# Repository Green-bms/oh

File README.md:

# OH!

OH! is a video magazine of Opensource Hardware projects streaming for free on @oh_video Youtube channel.

## 2024 edition
### Issue 01 - Play with NeoMatrix
Streaming release date: 02/01/2024 <br>

Youtube page: https://youtu.be/Kcz4IKiXUUs?si=wSDmESj03bVOOBnR <br>

In this issue we see how to program the WS2812B 8x8 RGB LED matrices.<br>

Resources: https://github.com/Green-bms/oh/tree/master/2024%20edition/Issue%201

### Issue 02 - Stop If Crash Watchdog
Streaming release date: 13/01/2024 <br>

Youtube page: https://youtu.be/fLkRN2xnHXY?si=DeNB-EbN8AmZp_JL <br>

In this issue I present my project "Stop If Crash", a simple Watchdog circuit based on IC NE555.
We will see together a simulation of the circuit, the design of the PCB with Kicad, the assembly with the functional test in the laboratory.<br>

Resources: https://github.com/Green-bms/oh/tree/master/2024%20edition/Issue%2002

### Issue 03 - OpticalShow
Streaming release date: 30/01/2024 <br>

Youtube page: https://youtu.be/mVdG0zdTeCE?si=hjvFPSwVRxgswea1 <br>

OpticalShow is a system that uses optical fibers to transmit the light emitted by an RGB LED matrix.
Each fiber is associated with its own LED and allows you to remote its RGB light to animate projects, such as panels, maps, artistic objects and wearables.
in this issue, in addition to describing the OpticalShow system, I show two application examples: "The world is mine!", a map of the world animated and illuminated by optical fibers and "Gloween Show" a small panel used in the Halloween party.<br>

Resources: 

- OpticalShow.
Hackaday: https://hackaday.io/project/189963-opticalshow<br>
Github: https://github.com/Green-bms/OpticalShow<br>
You can buy mask here: https://www.pcbway.com/project/shareproject/OpticalShow_mask_225f24a0.html<br>
You can buy card here: https://www.pcbway.com/project/shareproject/OpticalShow_card_PCB_6144c0a7.html<br>

- The World is mine.
https://www.instructables.com/The-World-Is-Mine/

- Gloween Show.
https://www.instructables.com/Gloween-Show/

### Issue 04 - CNC PCB milling
Streaming release date: 13/02/2024 <br>

Youtube page: https://www.youtube.com/watch?v=61v8TkvMFBA <br>
Make PCB with CNC milling machine <br>
In this issue I present to you my economical CNC milling machine Vevor CNC 3018 PRO, with which I started making PCBs for my simplest projects.
In addition to describing the milling machine, we will create a small step by step project together, from the CAD drawing of the PCB to the milling!<br>

If you also want to practice with the same PCB shown in the video, you can download all the CAD, CAM and CNC files from the following link:<br>
https://github.com/Green-bms/oh/tree/master/2024%20edition/Issue%2004 <br>

Opensource applications used :<br>
 - Kicad: https://www.kicad.org/ <br>
 - Flatcam: http://flatcam.org/ <br>
 - Candle: https://github.com/Denvi/Candle <br>

### Issue 05 - EV Lithium upgrades
Streaming release date: 27/02/2024 <br>

Youtube page: https://www.youtube.com/watch?v=jmhK0d0eKHg <br>
In this issue I take a trip back in time to tell you about my projects related to electric mobility.
Today there is a lot of talk about electric mobility.
I started to be interested in 2-wheeled electric vehicles in 2013, so I could go to work every day while polluting less!
I gave life back to 3 electric motorbikes that had exhausted batteries, transforming them into high-performance vehicles, with lithium batteries!
The vehicles I upgraded are:
E-tropolis Belair,
Vectrix Vx1 and e-max 110s

I have decided to share with you this exciting experience that lasted 10 years.

I have shared the documents of my upgrades at the following links:
https://github.com/Green-bms/oh/tree/master/2024%20edition/Issue%2005

### Issue 06 - Smart BMS (part 1)
Streaming release date: 12/03/2024 <br>

Youtube page: https://youtu.be/0NjMYVWZLLw?si=yNR26aHXIvKIdVsY <br>
In this issue I start to talk to you about my first Opensource project: Smart BMS - Battery Management System.<br>
I have shared the documents of the project at the following links: <br>
Github: https://github.com/Green-bms/SmartBMS <br>
Hackaday: https://hackaday.io/project/181453-green-bms <br>

### Issue 07 - Smart BMS (part 2)
Streaming release date: 26/03/2024 <br>

Youtube page: https://youtu.be/d0Qe47wP7eQ?si=s2jLH3D_zc0WCvRl  <br>
In this issue I continue to describe my first Opensource project: Smart BMS - Battery Management System <br>
I have shared the documents of the project at the following links: <br>
Github: https://github.com/Green-bms/SmartBMS <br>
Hackaday: https://hackaday.io/project/181453-green-bms <br>

### Issue 08 - Smart BMS (part 3)
Streaming release date: 09/04/2024 <br>

Youtube page: https://youtu.be/FND_0AVq5Ik?si=xOSsRHYRp_0sxjTm <br>
In this issue I continue to describe my first Opensource project: Smart BMS - Battery Management System <br>
I have shared the documents of the project at the following links: <br>
Github: https://github.com/Green-bms/SmartBMS <br>
Hackaday: https://hackaday.io/project/181453-green-bms <br>

### Issue 09 - Green Detect Wireless Sensor Network
Streaming release date: 23/04/2024 <br>

Youtube page: https://youtu.be/QgU09LJju4c?si=UmGGuCsF_K0YVous <br>
In this issue I describe my  Opensource project: Green Detect Wireless Sensor Network Platform (WSN) , for environmental monitoring. <br>
I have shared the documents of the project at the following links: <br>
Github:  https://github.com/Green-bms/GreenDetect <br>
Hackaday: https://hackaday.io/project/186064-green-detect <br>

### Issue 10 - Green Detect Windows application
Streaming release date: 07/05/2024 <br>

Youtube page: https://youtu.be/rTwm69dqrus?si=7FWuEQkdGhM1CUF- <br>
In this issue I describe the Green Detect application in detail.
I show you how to manage and configure the wireless sensor network. <br>
I have shared the documents of the project at the following links: <br>
Github:  https://github.com/Green-bms/GreenDetect <br>
Hackaday: https://hackaday.io/project/186064-green-detect <br>

### Issue 11 - Green Detect Windows application
Streaming release date: 21/05/2024 <br>

Youtube page: https://youtu.be/-PUpspmr6Rk?si=hIGa6V5kiF8c8neI <br>
This issue is dedicated to system tests, we will test a network with 60 modules, fault simulations and a working prototype on the balcony of my house! <br>
I have shared the documents of the project at the following links: <br>
Github:  https://github.com/Green-bms/GreenDetect <br>
Hackaday: https://hackaday.io/project/186064-green-detect <br>

## Warning
All projects, tests and experiments shown and shared in this repository may contain errors and malfunctions and are without warranty.

If you decide to make them, remember that it is at your own risk

The use of this project may not be compliant with local laws or regulations.

## License

This work is licensed under a **Creative Commons Attribution-ShareAlike 4.0 International License**.
https://creativecommons.org/licenses/by-sa/4.0/

### You are free to:

**Share** — copy and redistribute the material in any medium or format

**Adapt**  — remix, transform, and build upon the material
for any purpose, even commercially.
This license is acceptable for Free Cultural Works.
The licensor cannot revoke these freedoms as long as you follow the license terms.

### Under the following terms:

**Attribution** — You must give appropriate credit, provide a link to the license, and indicate if changes were made. You may do so in any reasonable manner, but not in any way that suggests the licensor endorses you or your use.

**ShareAlike** — If you remix, transform, or build upon the material, you must distribute your contributions under the same license as the original.

**No additional restrictions** — You may not apply legal terms or technological measures that legally restrict others from doing anything the license permits.

### Notices:
You do not have to comply with the license for elements of the material in the public domain or where your use is permitted by an applicable exception or limitation.
No warranties are given. The license may not give you all of the permissions necessary for your intended use. For example, other rights such as publicity, privacy, or moral rights may limit how you use the material.

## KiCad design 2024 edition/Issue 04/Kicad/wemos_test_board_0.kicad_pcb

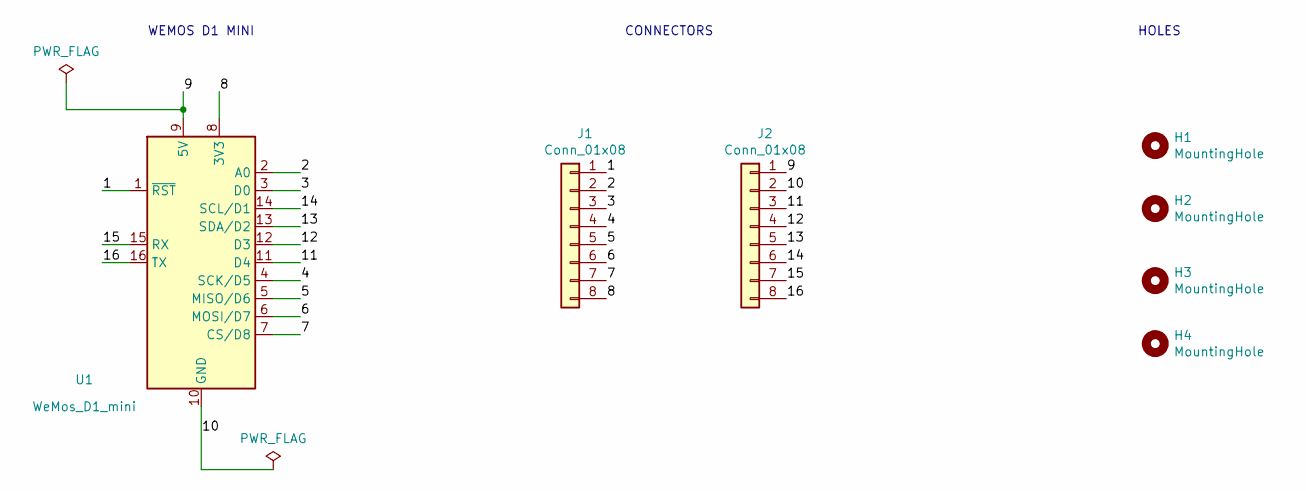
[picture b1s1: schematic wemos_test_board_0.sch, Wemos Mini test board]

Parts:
H1, H2, H3, H4: MountingHole; MountingHole_3.2mm_M3
J1, J2: Conn_01x08; TerminalBlock_Phoenix_PT-1,5-8-5.0-H_1x08_P5.00mm_Horizontal
U1: WeMos_D1_mini; WEMOS_D1_mini_light

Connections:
/1: J1.1, U1.1 (~RST)
/2: J1.2, U1.2 (A0)
/3: J1.3, U1.3 (D0)
/4: J1.4, U1.4 (SCK/D5)
/5: J1.5, U1.5 (MISO/D6)
/6: J1.6, U1.6 (MOSI/D7)
/7: J1.7, U1.7 (CS/D8)
/8: J1.8, U1.8 (3V3)
/9: J2.1, U1.9 (5V)
/10: J2.2, U1.10 (GND)
/11: J2.3, U1.11 (D4)
/12: J2.4, U1.12 (D3)
/13: J2.5, U1.13 (SDA/D2)
/14: J2.6, U1.14 (SCL/D1)
/15: J2.7, U1.15 (RX)
/16: J2.8, U1.16 (TX)

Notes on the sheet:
WEMOS D1 MINI
CONNECTORS
HOLES

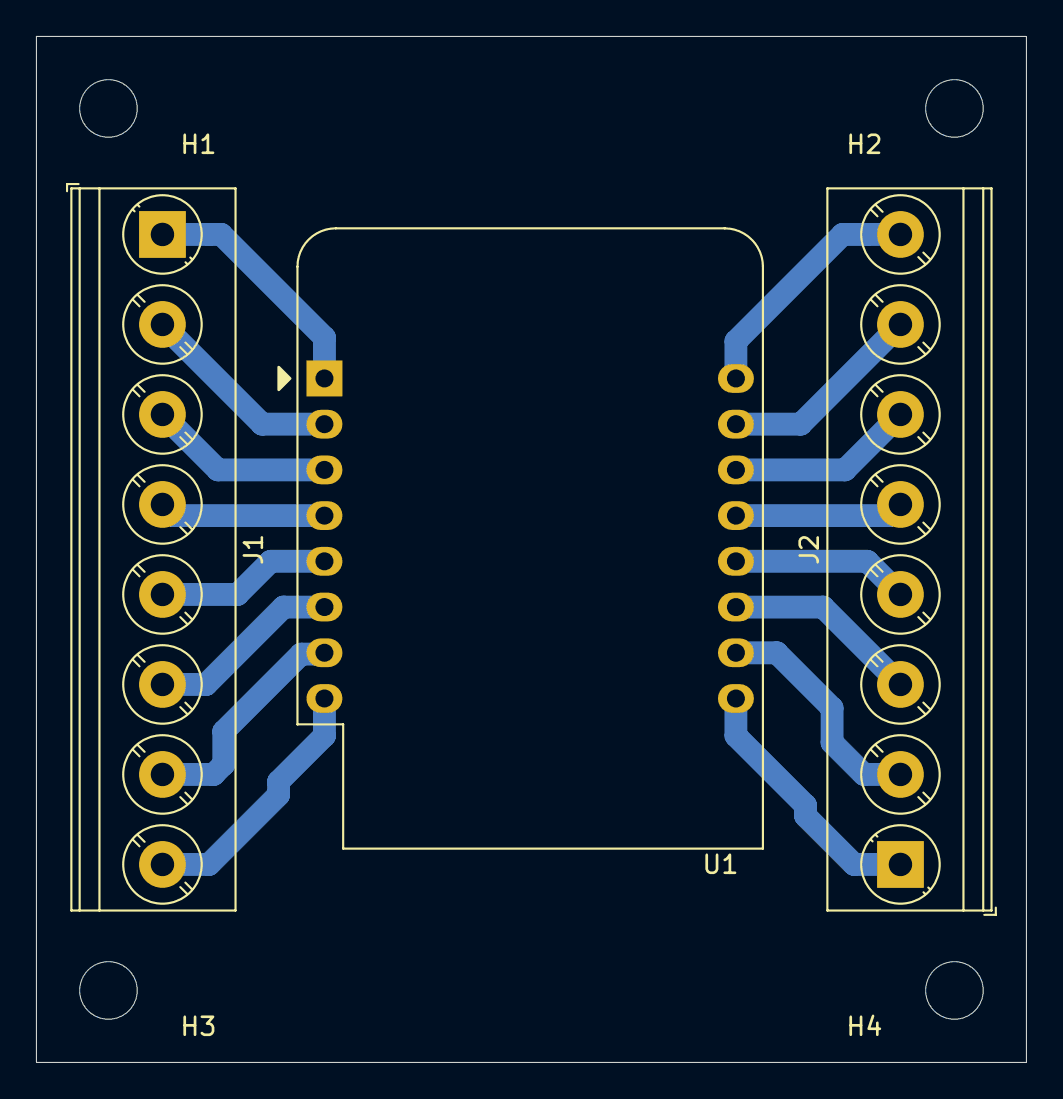
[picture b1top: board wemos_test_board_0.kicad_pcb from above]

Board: 2 copper layers, 55.0 x 57.0 mm, 7 parts (0 on the bottom side), 16 nets.

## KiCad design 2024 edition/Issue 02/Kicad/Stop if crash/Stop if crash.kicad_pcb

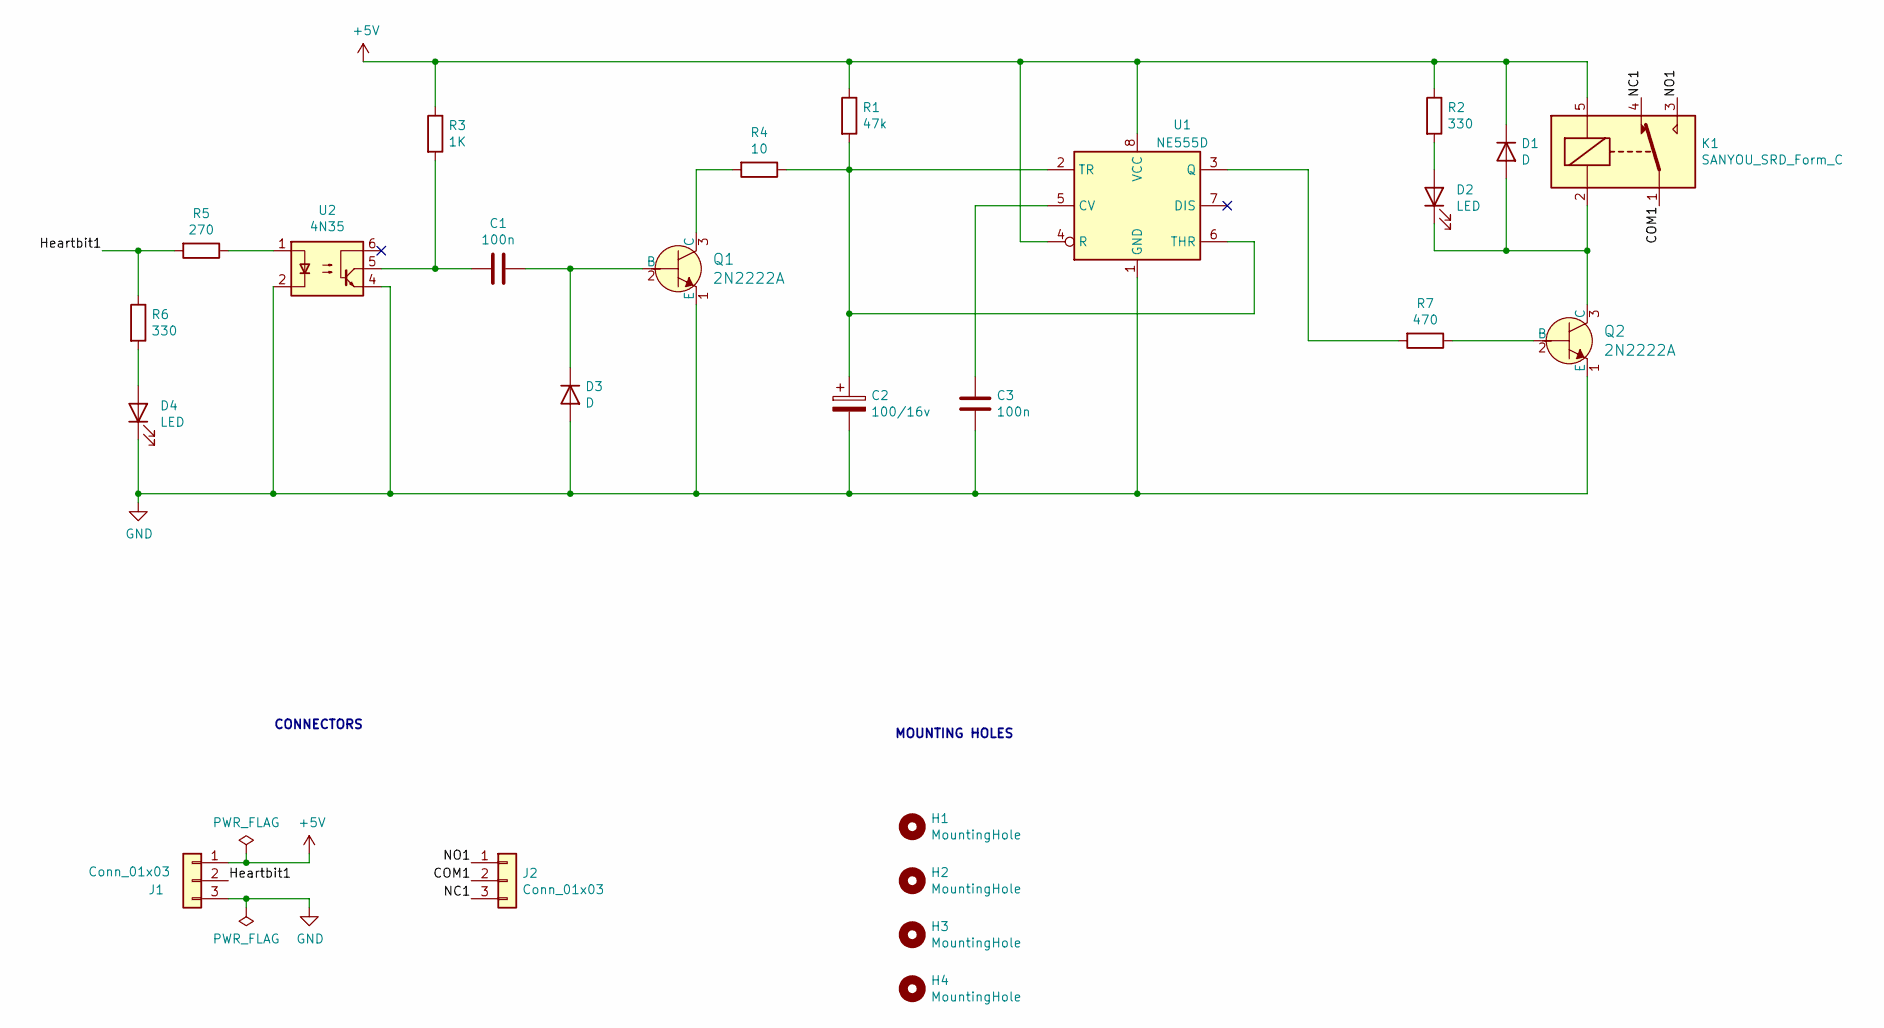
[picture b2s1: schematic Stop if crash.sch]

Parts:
C1, C3: 100n; C_Disc_D4.3mm_W1.9mm_P5.00mm
C2: 100/16v; CP_Radial_D8.0mm_P5.00mm
D1, D3: D; D_DO-15_P2.54mm_Vertical_AnodeUp
D2, D4: LED; LED_D3.0mm
H1, H2, H3, H4: MountingHole; MountingHole_3.2mm_M3
J1, J2: Conn_01x03; TerminalBlock_Phoenix_PT-1,5-3-5.0-H_1x03_P5.00mm_Horizontal
K1: SANYOU_SRD_Form_C; Relay_SPDT_SANYOU_SRD_Series_Form_C
Q1, Q2: 2N2222A; TO-92; MPN 2N2222A; Digi-Key_PN 2N2222ACS-ND
R1: 47k; R_Axial_DIN0207_L6.3mm_D2.5mm_P2.54mm_Vertical
R2, R6: 330; R_Axial_DIN0207_L6.3mm_D2.5mm_P2.54mm_Vertical
R3: 1K; R_Axial_DIN0207_L6.3mm_D2.5mm_P2.54mm_Vertical
R4: 10; R_Axial_DIN0207_L6.3mm_D2.5mm_P2.54mm_Vertical
R5: 270; R_Axial_DIN0207_L6.3mm_D2.5mm_P2.54mm_Vertical
R7: 470; R_Axial_DIN0207_L6.3mm_D2.5mm_P2.54mm_Vertical
U1: NE555D; DIP-8_W7.62mm
U2: 4N35; DIP-6_W7.62mm

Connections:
+5V: D1.1 (K), J1.1, K1.5, R1.1, R2.1, R3.1, U1.4 (R), U1.8 (VCC)
/COM1: J2.2, K1.1
/Heartbit1: J1.2, R5.2, R6.1
/NC1: J2.3, K1.4
/NO1: J2.1, K1.3
GND: C2.2, C3.2, D3.2 (A), D4.1 (K), J1.3, Q1.1 (E), Q2.1 (E), U1.1 (GND), U2.2, U2.4
unnamed: C1.1, D3.1 (K), Q1.2 (B)
unnamed: C1.2, R3.2, U2.5
unnamed: C2.1, R1.2, R4.1, U1.2 (TR), U1.6 (THR)
unnamed: C3.1, U1.5 (CV)
unnamed: D1.2 (A), D2.1 (K), K1.2, Q2.3 (C)
unnamed: D2.2 (A), R2.2
unnamed: D4.2 (A), R6.2
unnamed: Q1.3 (C), R4.2
unnamed: Q2.2 (B), R7.1
unnamed: R5.1, U2.1
unnamed: R7.2, U1.3 (Q)

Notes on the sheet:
CONNECTORS
MOUNTING HOLES

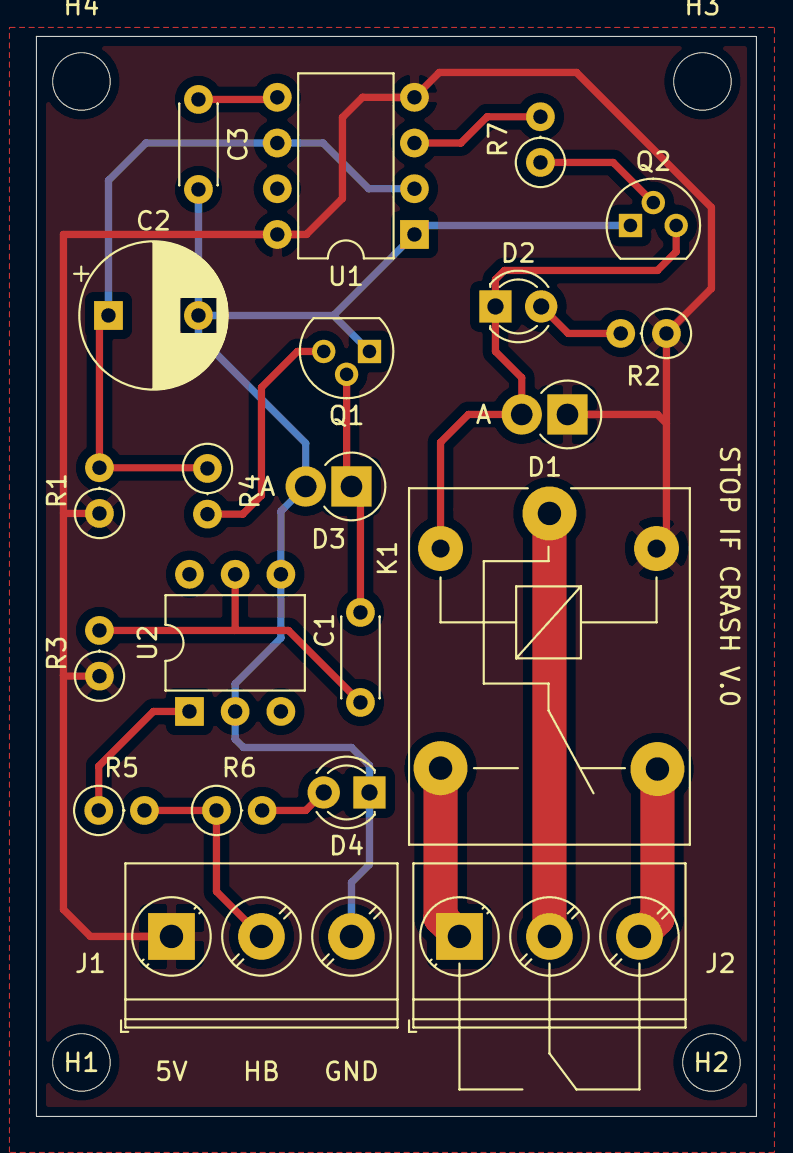
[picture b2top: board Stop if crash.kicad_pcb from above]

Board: 2 copper layers, 40.0 x 60.0 mm, 25 parts (0 on the bottom side), 17 nets.

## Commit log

2023-12-29 Update README.md
    Added 2024 Issue 1 info
2023-12-29 Update README.md
    added warning and license
2023-12-30 added Issue 5 documents
2024-01-13 Added Issue 2 files
2024-01-13 added Issue 2 info
2024-01-27 added Issue n.3
2024-02-10 Add files via upload
    added Issue 4 files
2024-02-10 Update README.md
    added Issue 4
2024-02-26 Update README.md
    added Issue 05
2024-03-14 Update README.md
    added Issue 06
2024-06-02 Update README.md
    added issues: 8,9,10,11
